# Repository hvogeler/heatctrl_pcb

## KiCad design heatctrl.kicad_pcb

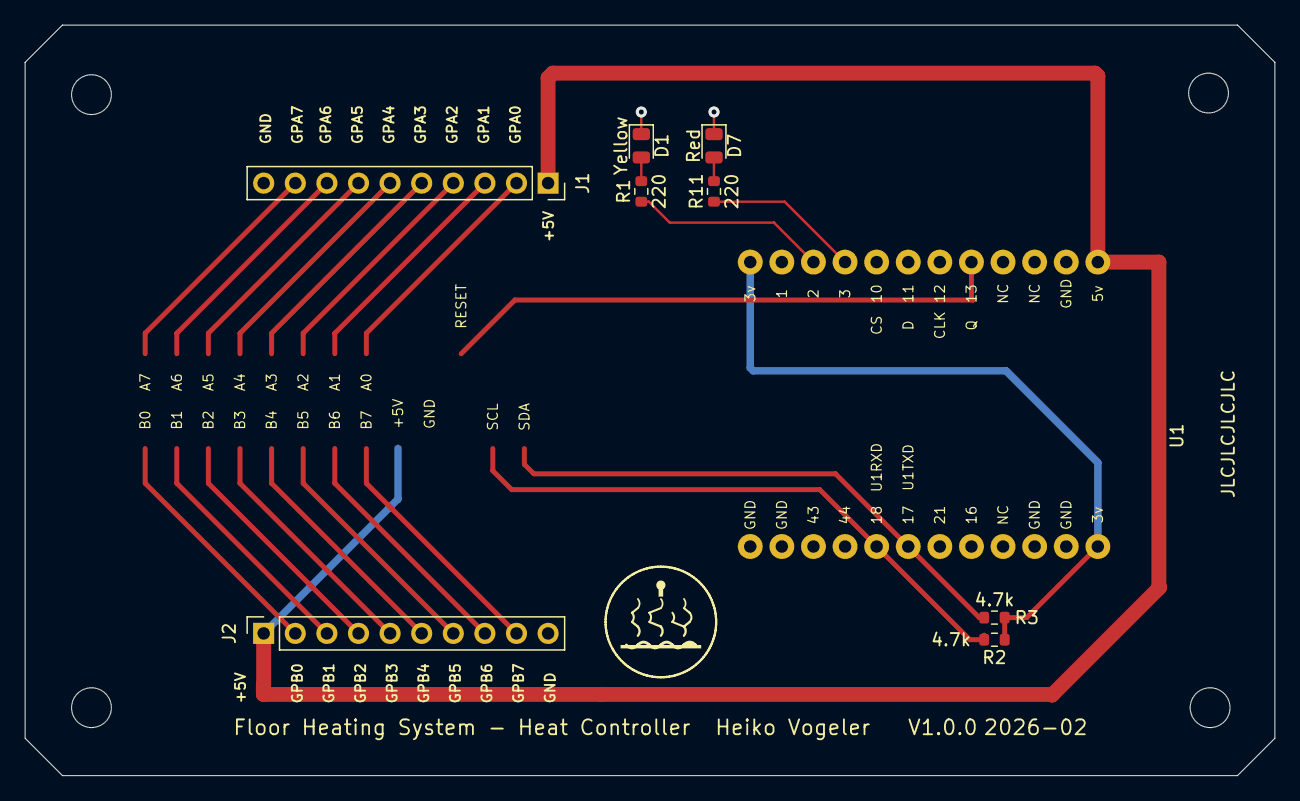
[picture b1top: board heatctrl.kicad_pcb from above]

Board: 2 copper layers, 100.5 x 60.3 mm, 9 parts (0 on the bottom side), 9 nets.

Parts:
D1: Yellow; LED_0805_2012Metric
D7: Red; LED_0805_2012Metric
J1, J2: Conn_01x10_Socket; PinSocket_1x10_P2.54mm_Vertical
R1, R11: 220; R_0603_1608Metric
R2, R3: 4.7k; R_0603_1608Metric
U1: T-Display-S3

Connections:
+3V3: R2.1, R3.1, U1.1 (3v), U1.24 (3v)
+5V: J1.1, J2.1, U1.12 (5V)
GND: D1.1, D7.1, J1.10, J2.10, U1.11 (GND), U1.13 (GND), U1.14 (GND), U1.22 (GND), U1.23 (GND)
unnamed: D1.2, R1.2
unnamed: D7.2, R11.2
unnamed: R1.1, U1.3 (2)
unnamed: R11.1, U1.4 (3)
SCL: R2.2, U1.17 (18)
SDA: R3.2, U1.18 (17)

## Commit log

2026-02-09 initial
2026-02-09 mcp and t-display-s3
2026-02-09 start pcb
2026-02-10 finigh 1 pcb
2026-02-11 THT components
2026-02-13 new boards
